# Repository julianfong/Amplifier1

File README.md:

# Amplifier1
Amplifier with low pass filter

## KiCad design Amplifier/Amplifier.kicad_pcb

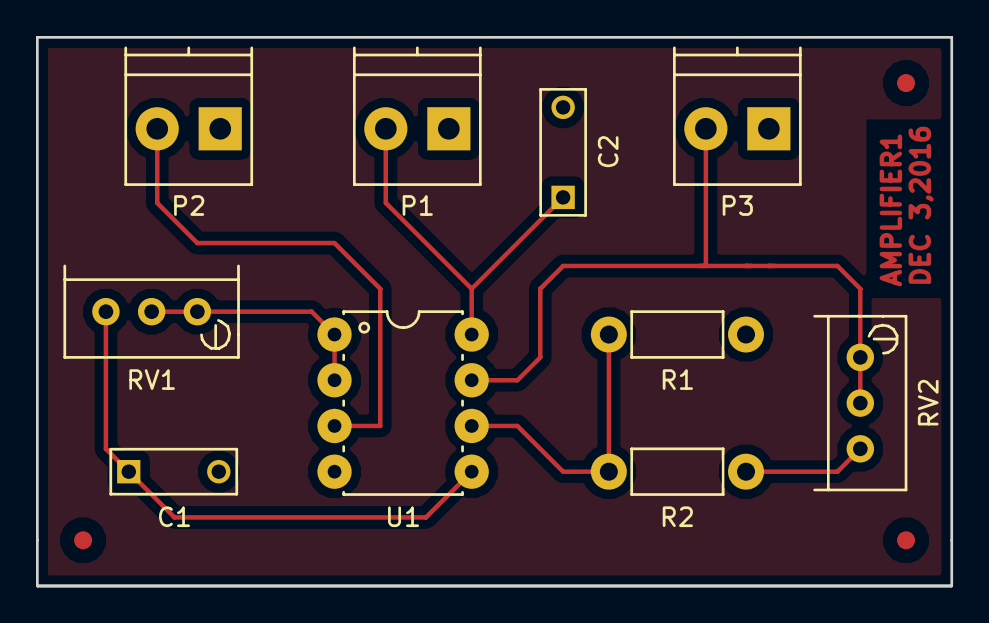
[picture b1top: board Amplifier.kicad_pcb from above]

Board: 2 copper layers, 50.8 x 30.5 mm, 10 parts (0 on the bottom side), 8 nets.

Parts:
C1: 100pF; C_Rect_L7_W2.5_P5
C2: 100nF; C_Rect_L7_W2.5_P5
P1, P2, P3: CONN_01X02; TerminalBlock_Pheonix_PT-3.5mm_2pol
R1, R2: 5k; Resistor_Horizontal_RM7mm
RV1: 10k; Potentiometer_Bourns_3296W_3-8Zoll_Inline_ScrewUp
RV2: 5k; Potentiometer_Bourns_3296W_3-8Zoll_Inline_ScrewUp
U1: MCP6002; PDIP-8

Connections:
+5V: C2.1, P1.2, U1.8
GND: C1.2, C2.2, P1.1, P2.1, P3.1, R1.2, U1.4
unnamed: C1.1, RV1.3, U1.5
unnamed: P2.2, U1.3
unnamed: P3.2, RV2.1, RV2.2, U1.7
unnamed: R1.1, R2.2, U1.6
unnamed: R2.1, RV2.3
unnamed: RV1.1, RV1.2, U1.1, U1.2

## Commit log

2016-12-04 Add files via upload
    Initial Upload,
2016-12-04 Add files via upload
    including Resume
